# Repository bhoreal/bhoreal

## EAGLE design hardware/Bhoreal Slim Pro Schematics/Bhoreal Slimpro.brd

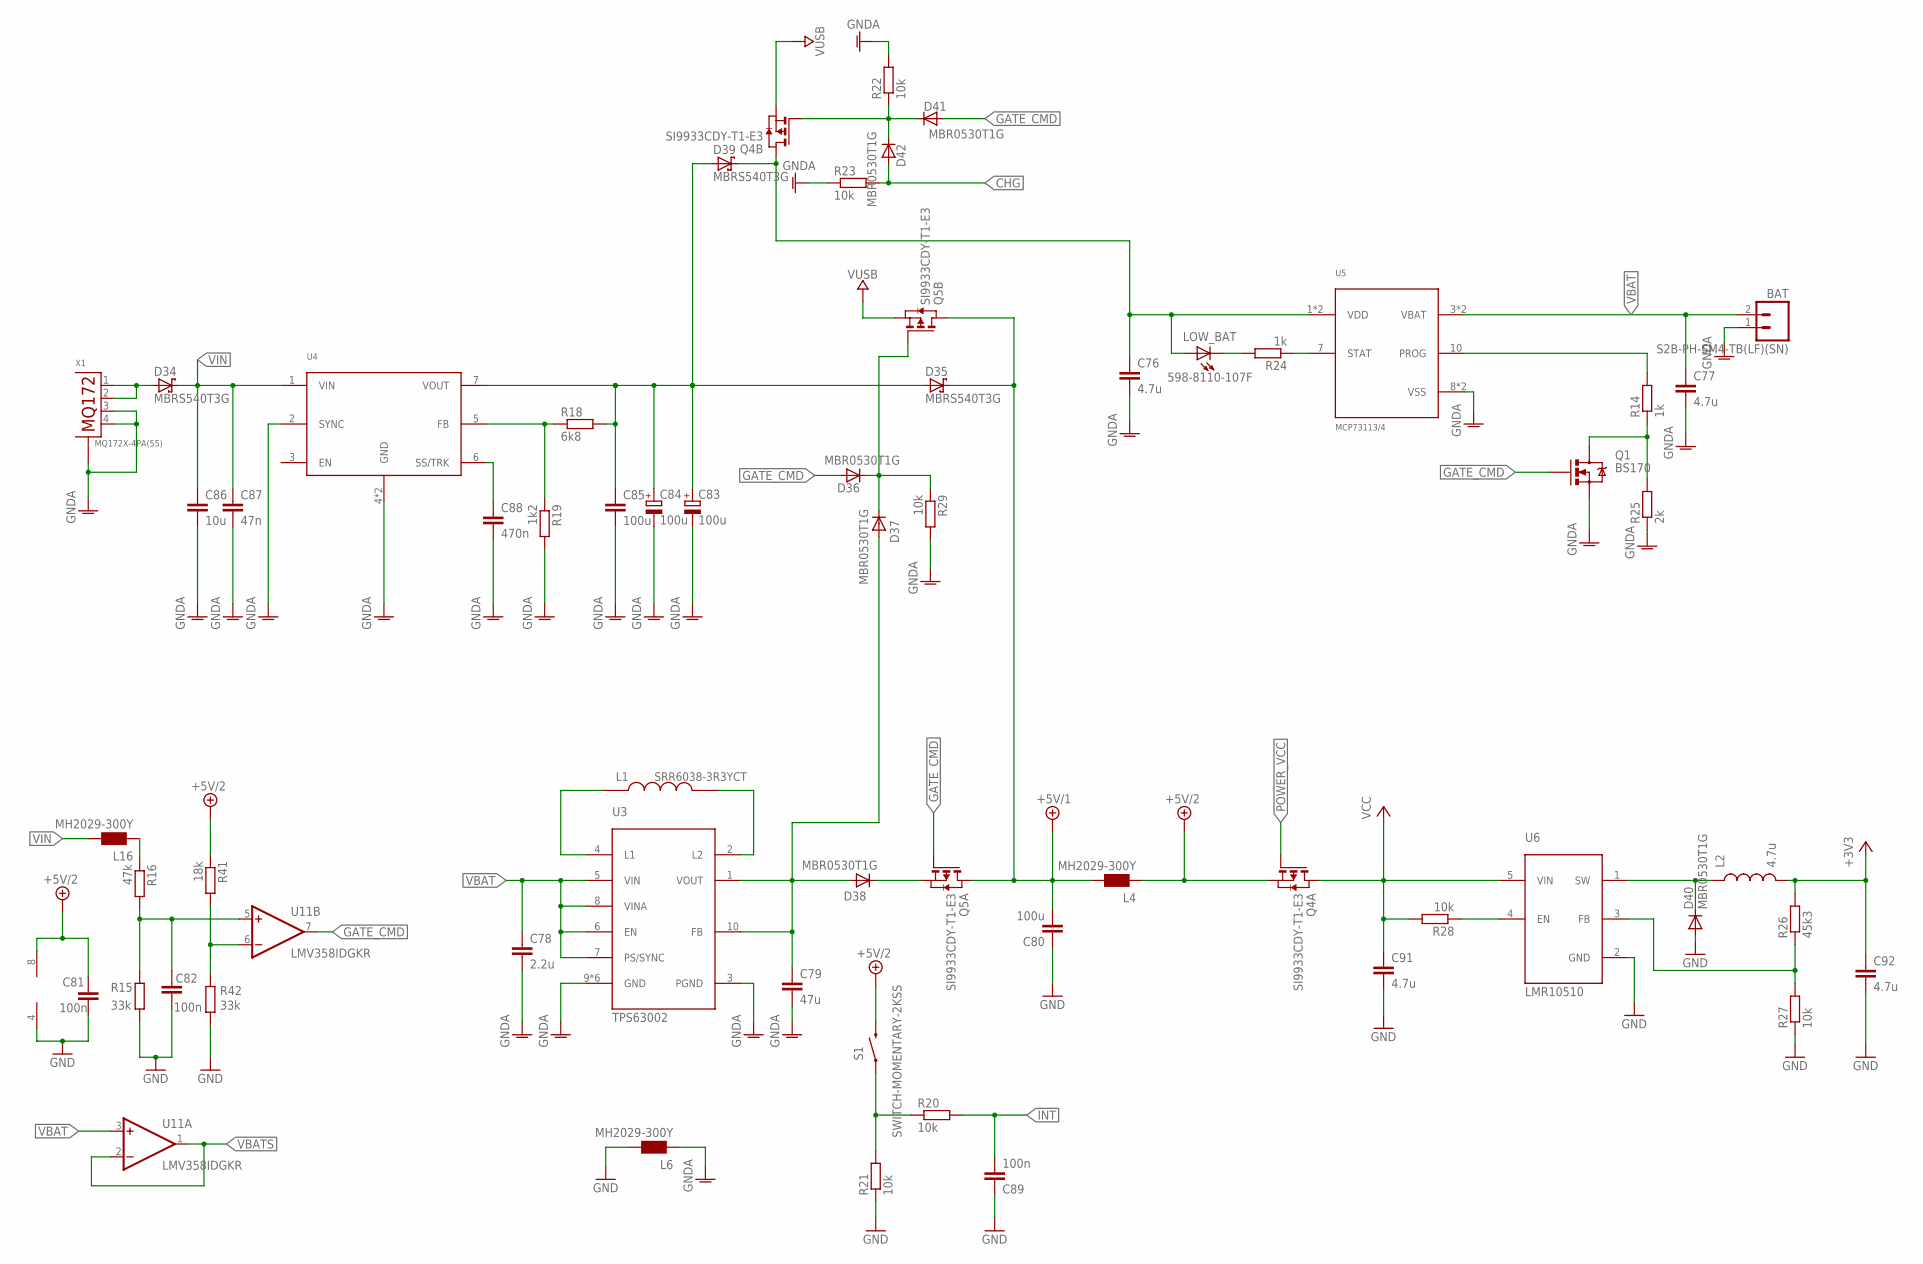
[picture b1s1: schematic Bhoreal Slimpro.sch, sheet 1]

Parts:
BAT: S2B-PH-SM4-TB(LF)(SN); S2B-PH
C76, C77: 4.7u; C0805
C78: 2.2u; C0805
C79: 47u; C1812
C80: 100u; C1206
C81, C82, C89: 100n; C0603
C83, C84: 100u; D/7343-31R
C85: 100u; C1210
C86: 10u; C1210
C87: 47n; C1206
C88: 470n; C0805
C91, C92: 4.7u; C0603
D34, D35, D39: MBRS540T3G; SMC
D36, D37, D38, D40, D41, D42: MBR0530T1G; SOD123
L1: SRR6038-3R3YCT; SRR6038
L2: 4.7u; 1210
L4, L6, L16: MH2029-300Y; 0805
LOW_BAT: 598-8110-107F; CHIP-LED0805
Q1: BS170; SOT23
Q4, Q5: SI9933CDY-T1-E3; SO8
R14, R24: 1k; R0603
R15, R42: 33k; R0603
R16: 47k; R0603
R18: 6k8; R0603
R19: 1k2; R0603
R20, R21, R22, R23, R27, R28, R29: 10k; R0603
R25: 2k; R0603
R26: 45k3; R0603
R41: 18k; R0603
S1: SWITCH-MOMENTARY-2KSS; KSS241G
U3: TPS63002; QFN-10_PAD
U4: LMZ2200X; TO-PMOD
U5: MCP73113/4; DFN-10
U6: LMR10510; SOT23-5L
U11: LMV358IDGKR; MSOP08
X1: MQ172X-4PA(55)

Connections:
+3V3: C92.1, L2.2, R26.2; also elsewhere on the board
+5V/1: C80.2, D35.C, L4.2, Q5.5 (D), Q5.6 (D), Q5.7 (D), Q5.8 (D); also elsewhere on the board
+5V/2: C81.1, L4.1, Q4.1 (S), R41.1, S1.2, U11.8 (V+); also elsewhere on the board
CHG: D42.A, R23.2; also elsewhere on the board
CMP: C82.2, R15.1, R16.2, U11.5 (+IN)
GATE_CMD: D36.A, D41.A, Q1.1 (G), Q5.2 (G), U11.7 (OUT); also elsewhere on the board
GND: C80.1, C81.2, C82.1, C89.1, C91.2, C92.2, D40.A, L6.2, R15.2, R21.1, R27.1, R42.2, U6.2 (GND), U11.4 (V-); also elsewhere on the board
GNDA: BAT.1, C76.2, C77.2, C78.2, C79.2, C83.-, C84.-, C85.2, C86.2, C87.2, C88.2, L6.1, Q1.2 (S), R19.2, R22.2, R23.1, R25.1, R29.2, U3.3 (PGND), U3.9 (GND), U3.11 (GND), U3.12 (GND), U3.13 (GND), U3.14 (GND), U3.15 (GND), U4.2 (SYNC), U4.4 (GND), U4.8 (GND), U5.8 (VSS), U5.9 (VSS), X1.3, X1.4, X1.P$1, X1.P$2; also elsewhere on the board
INT: C89.2, R20.2; also elsewhere on the board
unnamed: R41.2, R42.1, U11.6 (-IN)
unnamed: D41.C, D42.C, Q4.4 (G), R22.1
unnamed: R14.2, U5.10 (PROG)
unnamed: L1.P$1 (1), U3.4 (L1)
unnamed: L1.P$2 (2), U3.2 (L2)
unnamed: D34.A, X1.1, X1.2
unnamed: C79.1, D37.A, D38.A, U3.1 (VOUT), U3.10 (FB)
unnamed: C76.1, D39.C, LOW_BAT.A, Q4.5 (D), Q4.6 (D), U5.1 (VDD), U5.2 (VDD)
unnamed: C83.+, C84.+, C85.1, D35.A, D39.A, R18.2, U4.7 (VOUT)
unnamed: R18.1, R19.1, U4.5 (FB)
unnamed: C88.1, U4.6 (SS/TRK)
unnamed: R20.1, R21.2, S1.1
unnamed: D36.C, D37.C, Q5.4 (G), R29.1
unnamed: LOW_BAT.C, R24.2
unnamed: R24.1, U5.7 (STAT)
unnamed: Q1.3 (D), R14.1, R25.2
unnamed: D40.C, L2.1, U6.1 (SW)
unnamed: R28.1, U6.4 (EN)
unnamed: R26.1, R27.2, U6.3 (FB)
unnamed: D38.C, Q5.1 (S)
unnamed: L16.1, R16.1
POWER_VCC: Q4.2 (G); also elsewhere on the board
VBAT: BAT.2, C77.1, C78.1, U3.5 (VIN), U3.6 (EN), U3.7 (PS/SYNC), U3.8 (VINA), U5.3 (VBAT), U5.4 (VBAT), U11.3 (+IN)
VBATS: U11.1 (OUT), U11.2 (-IN); also elsewhere on the board
VCC: C91.1, Q4.7 (D), Q4.8 (D), R28.2, U6.5 (VIN); also elsewhere on the board
VIN: C86.1, C87.1, D34.C, L16.2, U4.1 (VIN)
VUSB: Q4.3 (S), Q5.3 (S); also elsewhere on the board

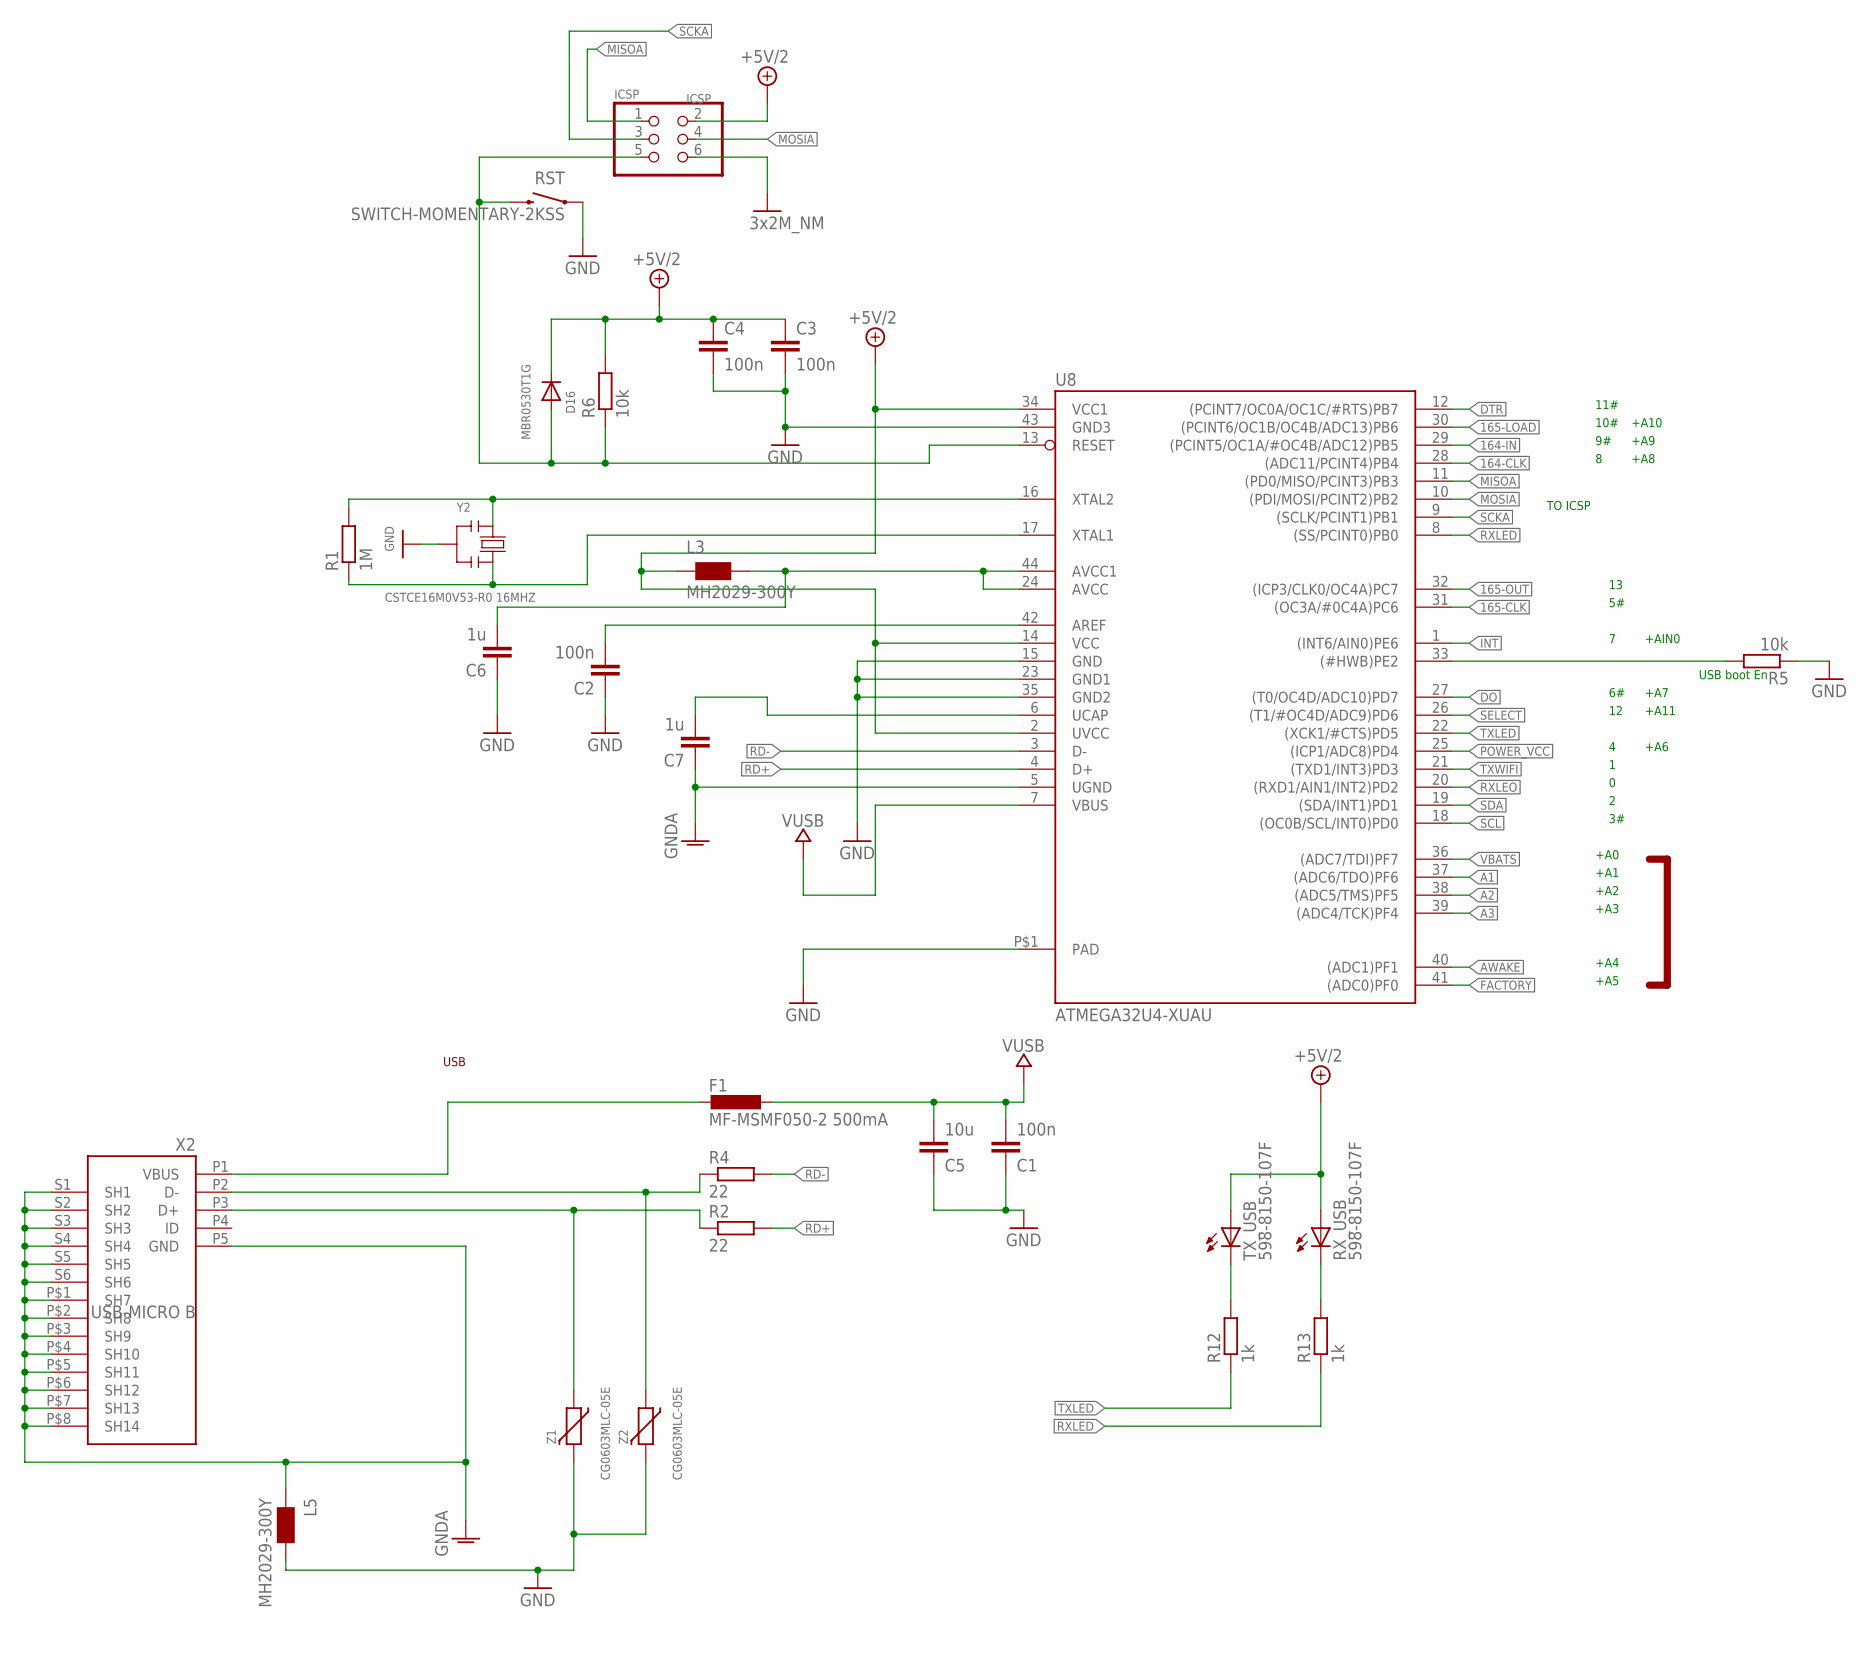
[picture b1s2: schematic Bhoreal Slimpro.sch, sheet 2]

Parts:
C1, C2, C3, C4: 100n; C0603
C5: 10u; C0805
C6, C7: 1u; C0805
D16: MBR0530T1G; SOD123
F1: MF-MSMF050-2 500mA; L1812
ICSP: ICSP; 2X03
L3, L5: MH2029-300Y; 0805
R1: 1M; R0603
R2, R4: 22; R0603
R5, R6: 10k; R0603
R12, R13: 1k; R0603
RST: SWITCH-MOMENTARY-2KSS; KSS241G
RX_USB: 598-8150-107F; CHIPLED_0805
TX_USB: 598-8150-107F; CHIPLED_0805
U8: ATMEGA32U4-XUAU; TQFP44-PAD
X2: USB-MICRO B; CON2_USB_MICRO_B_AT
Y2: CSTCE16M0V53-R0 16MHZ; RESONATOR
Z1, Z2: CG0603MLC-05E; CT/CN0603

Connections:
164-CLK: U8.28 ((ADC11/PCINT4)PB4); also elsewhere on the board
164-IN: U8.29 ((PCINT5/OC1A/#OC4B/ADC12)PB5); also elsewhere on the board
165-CLK: U8.31 ((OC3A/#0C4A)PC6); also elsewhere on the board
165-LOAD: U8.30 ((PCINT6/OC1B/OC4B/ADC13)PB6); also elsewhere on the board
165-OUT: U8.32 ((ICP3/CLK0/OC4A)PC7); also elsewhere on the board
+5V/2: C3.1, C4.1, D16.C, ICSP.2, L3.1, R6.2, RX_USB.A, TX_USB.A, U8.2 (UVCC), U8.14 (VCC), U8.34 (VCC1); also elsewhere on the board
A1: U8.37 ((ADC6/TDO)PF6)
A2: U8.38 ((ADC5/TMS)PF5)
A3: U8.39 ((ADC4/TCK)PF4)
AREF: C2.2, U8.42 (AREF)
AVCC: C6.2, L3.2, U8.24 (AVCC), U8.44 (AVCC1)
AWAKE: U8.40 ((ADC1)PF1); also elsewhere on the board
D+: R2.1, X2.P3 (D+), Z1.1
D-: R4.1, X2.P2 (D-), Z2.1
DO: U8.27 ((T0/OC4D/ADC10)PD7); also elsewhere on the board
DTR: U8.12 ((PCINT7/OC0A/OC1C/#RTS)PB7); also elsewhere on the board
FACTORY: U8.41 ((ADC0)PF0); also elsewhere on the board
GND: C1.1, C2.1, C3.2, C4.2, C5.1, C6.1, ICSP.6, L5.2, R5.1, RST.1, U8.15 (GND), U8.23 (GND1), U8.35 (GND2), U8.43 (GND3), U8.P$1 (PAD), Y2.2, Z1.2, Z2.2; also elsewhere on the board
GNDA: C7.1, L5.1, U8.5 (UGND), X2.P5 (GND), X2.P$1 (SH7), X2.P$2 (SH8), X2.P$3 (SH9), X2.P$4 (SH10), X2.P$5 (SH11), X2.P$6 (SH12), X2.P$7 (SH13), X2.P$8 (SH14), X2.S1 (SH1), X2.S2 (SH2), X2.S3 (SH3), X2.S4 (SH4), X2.S5 (SH5), X2.S6 (SH6); also elsewhere on the board
HWB: R5.2, U8.33 ((#HWB)PE2)
INT: U8.1 ((INT6/AIN0)PE6); also elsewhere on the board
MISOA: ICSP.1, U8.11 ((PD0/MISO/PCINT3)PB3)
MOSIA: ICSP.4, U8.10 ((PDI/MOSI/PCINT2)PB2)
unnamed: R12.2, TX_USB.C
unnamed: R13.2, RX_USB.C
POWER_VCC: U8.25 ((ICP1/ADC8)PD4); also elsewhere on the board
RD+: R2.2, U8.4 (D+)
RD-: R4.2, U8.3 (D-)
RST: D16.A, ICSP.5, R6.1, RST.2, U8.13 (RESET); also elsewhere on the board
RXLED: R13.1, U8.8 ((SS/PCINT0)PB0)
RXLEO: U8.20 ((RXD1/AIN1/INT2)PD2); also elsewhere on the board
SCKA: ICSP.3, U8.9 ((SCLK/PCINT1)PB1)
SCL: U8.18 ((OC0B/SCL/INT0)PD0); also elsewhere on the board
SDA: U8.19 ((SDA/INT1)PD1); also elsewhere on the board
SELECT: U8.26 ((T1/#OC4D/ADC9)PD6); also elsewhere on the board
TXLED: R12.1, U8.22 ((XCK1/#CTS)PD5)
TXWIFI: U8.21 ((TXD1/INT3)PD3); also elsewhere on the board
UCAP: C7.2, U8.6 (UCAP)
VBATS: U8.36 ((ADC7/TDI)PF7); also elsewhere on the board
VUSB: C1.2, C5.2, F1.1, U8.7 (VBUS); also elsewhere on the board
XTAL3: R1.2, U8.16 (XTAL2), Y2.1
XTAL4: R1.1, U8.17 (XTAL1), Y2.3
XUSB: F1.2, X2.P1 (VBUS)

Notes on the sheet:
USB boot En
USB
TO ICSP
10#
11#
+A6
+A11
+A10
+A9
+A7
+A8
+AIN0
+A0
+A1
+A2
+A3
+A4
+A5

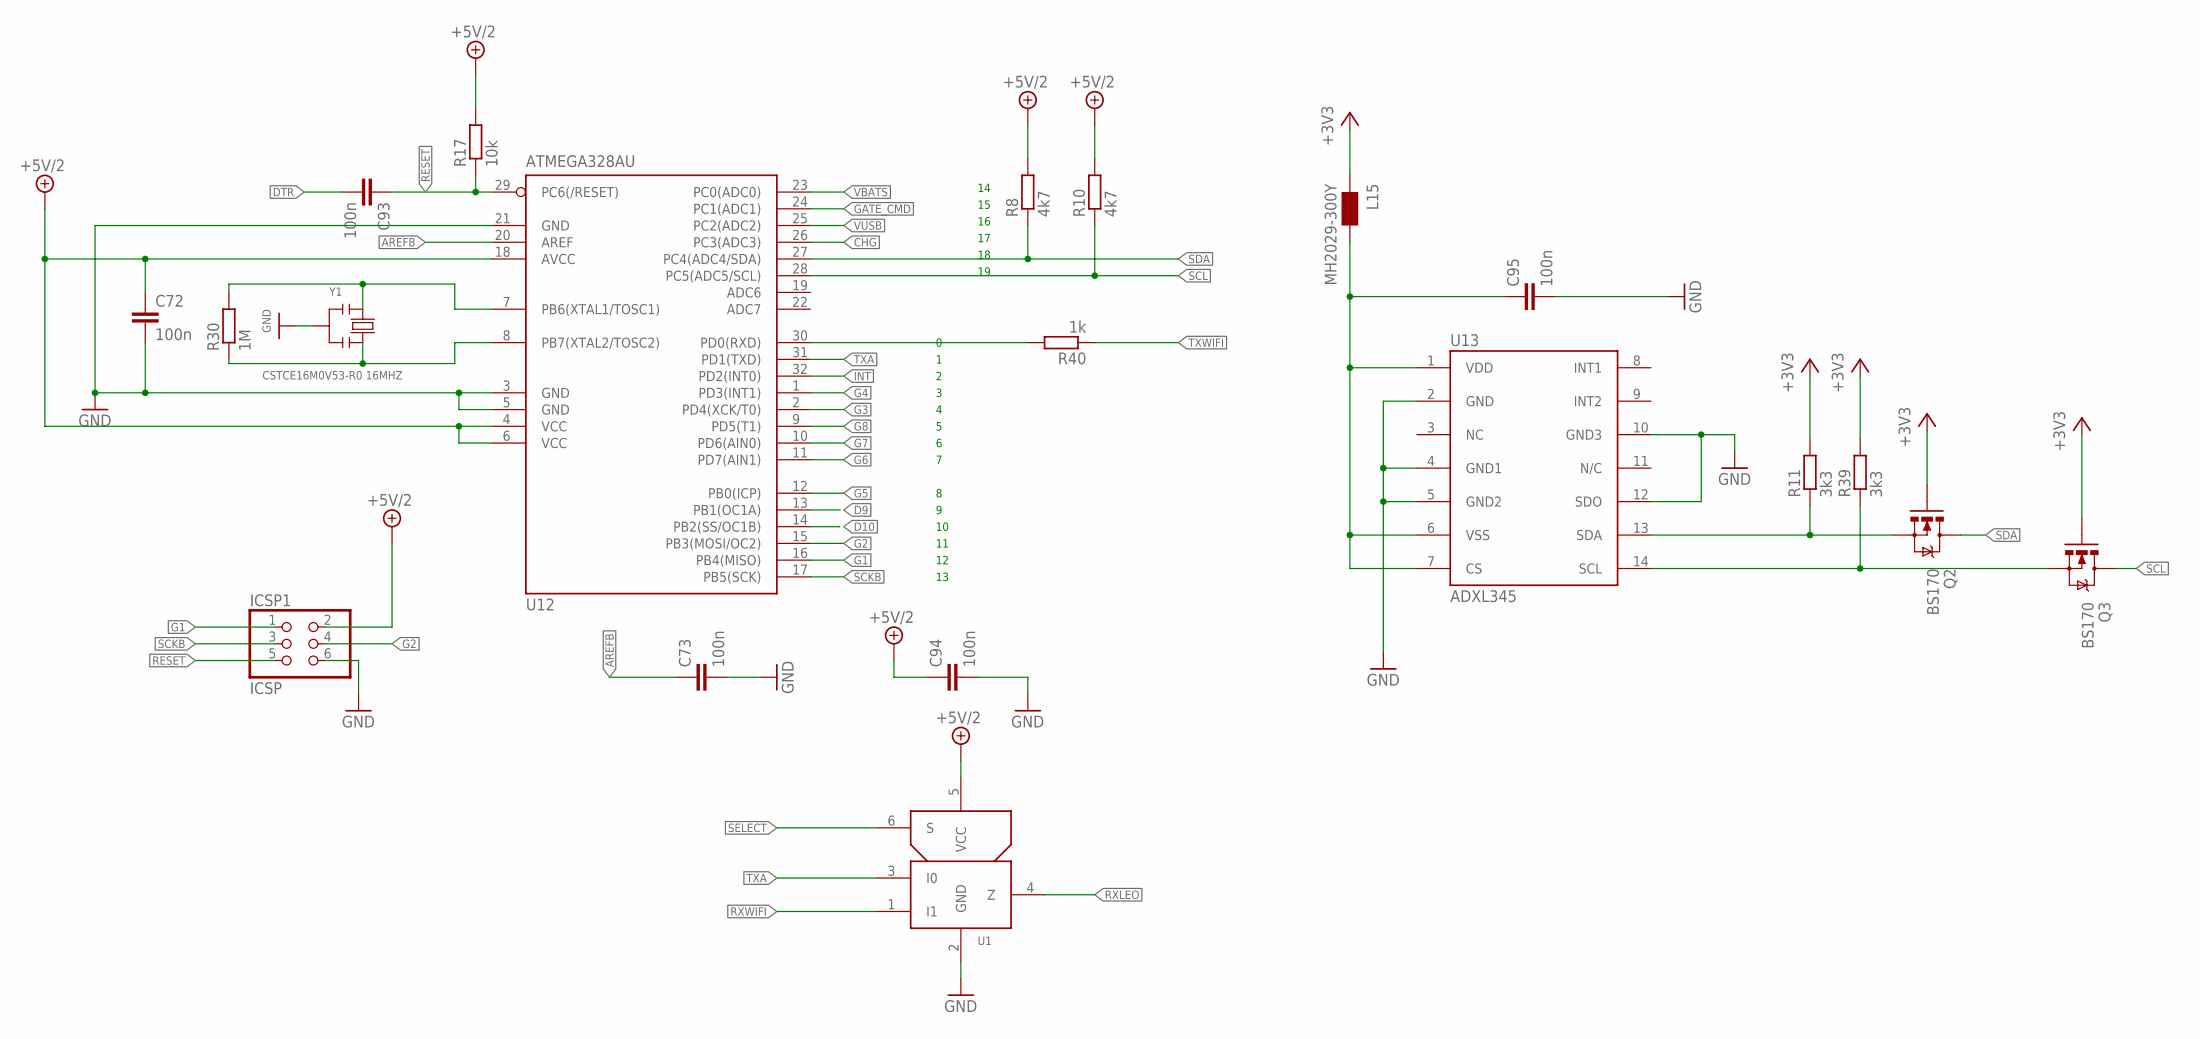
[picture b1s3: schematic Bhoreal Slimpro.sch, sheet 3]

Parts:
C72, C73, C93, C94, C95: 100n; C0603
ICSP1: ICSP; 2X03
L15: MH2029-300Y; 0805
Q2, Q3: BS170; SOT23
R8, R10: 4k7; R0603
R11, R39: 3k3; R0603
R17: 10k; R0603
R30: 1M; R0603
R40: 1k; R0603
U1: NC7SZ157P6X; SC70
U12: ATMEGA328AU; TQFP32-08
U13: ADXL345; LGA14
Y1: CSTCE16M0V53-R0 16MHZ; RESONATOR

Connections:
+3V3: L15.1, Q2.1 (G), Q3.1 (G), R11.2, R39.2; also elsewhere on the board
+5V/2: C72.1, C94.1, ICSP1.2, R8.2, R10.2, R17.2, U1.5 (VCC), U12.4 (VCC), U12.6 (VCC), U12.18 (AVCC); also elsewhere on the board
AREFB: C73.1, U12.20 (AREF)
CHG: U12.26 (PC3(ADC3)); also elsewhere on the board
D9: U12.13 (PB1(OC1A))
D10: U12.14 (PB2(SS/OC1B))
DTR: C93.2; also elsewhere on the board
G1: ICSP1.1, U12.16 (PB4(MISO)); also elsewhere on the board
G2: ICSP1.4, U12.15 (PB3(MOSI/OC2)); also elsewhere on the board
G3: U12.2 (PD4(XCK/T0)); also elsewhere on the board
G4: U12.1 (PD3(INT1)); also elsewhere on the board
G5: U12.12 (PB0(ICP)); also elsewhere on the board
G6: U12.11 (PD7(AIN1)); also elsewhere on the board
G7: U12.10 (PD6(AIN0)); also elsewhere on the board
G8: U12.9 (PD5(T1)); also elsewhere on the board
GATE_CMD: U12.24 (PC1(ADC1)); also elsewhere on the board
GND: C72.2, C73.2, C94.2, C95.2, ICSP1.6, U1.2 (GND), U12.3 (GND), U12.5 (GND), U12.21 (GND), U13.2 (GND), U13.4 (GND1), U13.5 (GND2), U13.10 (GND3), U13.12 (SDO), Y1.2; also elsewhere on the board
INT: U12.32 (PD2(INT0)); also elsewhere on the board
unnamed: C95.1, L15.2, U13.1 (VDD), U13.6 (VSS), U13.7 (CS)
unnamed: Q2.2 (S), R11.1, U13.13 (SDA)
unnamed: Q3.2 (S), R39.1, U13.14 (SCL)
RESET: C93.1, ICSP1.5, R17.1, U12.29 (PC6(/RESET))
RXA: R40.2, U12.30 (PD0(RXD))
RXLEO: U1.4 (Z); also elsewhere on the board
RXWIFI: U1.1 (I1); also elsewhere on the board
SCKB: ICSP1.3, U12.17 (PB5(SCK))
SCL: Q3.3 (D), R10.1, U12.28 (PC5(ADC5/SCL)); also elsewhere on the board
SDA: Q2.3 (D), R8.1, U12.27 (PC4(ADC4/SDA)); also elsewhere on the board
SELECT: U1.6 (S); also elsewhere on the board
TXA: U1.3 (I0), U12.31 (PD1(TXD))
TXWIFI: R40.1; also elsewhere on the board
VBATS: U12.23 (PC0(ADC0)); also elsewhere on the board
VUSB: U12.25 (PC2(ADC2)); also elsewhere on the board
XTAL1: R30.2, U12.7 (PB6(XTAL1/TOSC1)), Y1.1
XTAL2: R30.1, U12.8 (PB7(XTAL2/TOSC2)), Y1.3

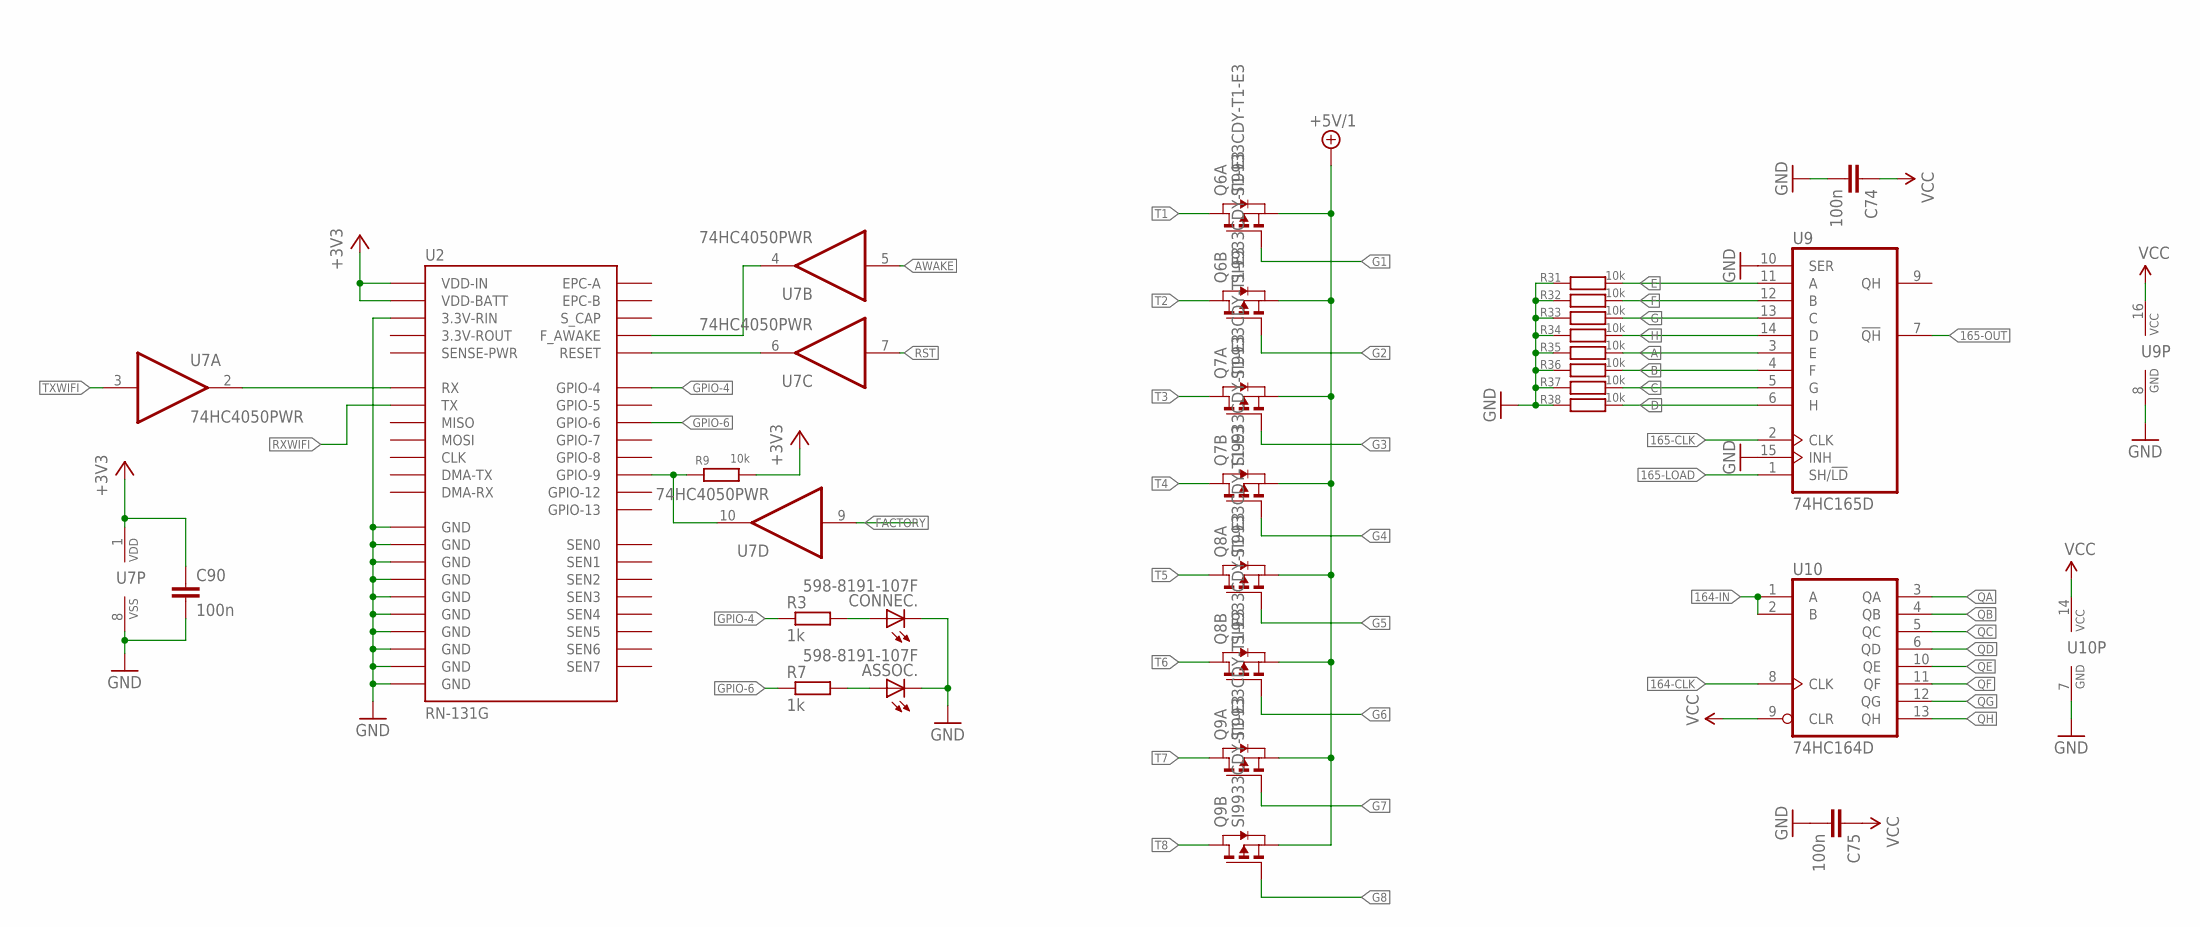
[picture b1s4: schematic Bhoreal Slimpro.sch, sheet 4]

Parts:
ASSOC.: 598-8191-107F; CHIP-LED0805
C74, C75, C90: 100n; C0603
CONNEC.: 598-8191-107F; CHIP-LED0805
Q6, Q7, Q8, Q9: SI9933CDY-T1-E3; SO8
R3, R7: 1k; R0603
R9, R31, R32, R33, R34, R35, R36, R37, R38: 10k; R0603
U2: RN-131G
U7: 74HC4050PWR; TSSOP16
U9: 74HC165D; SO16
U10: 74HC164D; SO14

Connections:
164-CLK: U10.8 (CLK); also elsewhere on the board
164-IN: U10.1 (A), U10.2 (B); also elsewhere on the board
165-CLK: U9.2 (CLK); also elsewhere on the board
165-LOAD: U9.1 (SH/!LD); also elsewhere on the board
165-OUT: U9.7 (!QH); also elsewhere on the board
+3V3: C90.1, R9.2, U2.P$20 (VDD-BATT), U2.P$21 (VDD-IN), U7.1 (VDD); also elsewhere on the board
+5V/1: Q6.1 (S), Q6.3 (S), Q7.1 (S), Q7.3 (S), Q8.1 (S), Q8.3 (S), Q9.1 (S), Q9.3 (S); also elsewhere on the board
A: R35.2, U9.3 (E); also elsewhere on the board
AWAKE: U7.5 (I); also elsewhere on the board
B: R36.2, U9.4 (F); also elsewhere on the board
C: R37.2, U9.5 (G); also elsewhere on the board
D: R38.2, U9.6 (H); also elsewhere on the board
E: R31.2, U9.11 (A); also elsewhere on the board
F: R32.2, U9.12 (B); also elsewhere on the board
FACTORY: U7.9 (I); also elsewhere on the board
G: R33.2, U9.13 (C); also elsewhere on the board
G1: Q6.2 (G); also elsewhere on the board
G2: Q6.4 (G); also elsewhere on the board
G3: Q7.2 (G); also elsewhere on the board
G4: Q7.4 (G); also elsewhere on the board
G5: Q8.2 (G); also elsewhere on the board
G6: Q8.4 (G); also elsewhere on the board
G7: Q9.2 (G); also elsewhere on the board
G8: Q9.4 (G); also elsewhere on the board
GND: ASSOC..C, C74.2, C75.2, C90.2, CONNEC..C, R31.1, R32.1, R33.1, R34.1, R35.1, R36.1, R37.1, R38.1, U2.P$18 (3.3V-RIN), U2.P$19 (GND), U2.P$36 (GND), U2.P$37 (GND), U2.P$38 (GND), U2.P$39 (GND), U2.P$40 (GND), U2.P$41 (GND), U2.P$42 (GND), U2.P$43 (GND), U2.P$44 (GND), U7.8 (VSS), U9.8 (GND), U9.10 (SER), U9.15 (INH), U10.7 (GND); also elsewhere on the board
GPIO-4: R3.1, U2.P$29 (GPIO-4)
GPIO-6: R7.1, U2.P$27 (GPIO-6)
H: R34.2, U9.14 (D); also elsewhere on the board
unnamed: CONNEC..A, R3.2
unnamed: ASSOC..A, R7.2
unnamed: U2.P$12 (RX), U7.2 (O)
unnamed: R9.1, U2.P$24 (GPIO-9), U7.10 (O)
unnamed: U2.P$9 (F_AWAKE), U7.4 (O)
unnamed: U2.P$5 (RESET), U7.6 (O)
QA: U10.3 (QA); also elsewhere on the board
QB: U10.4 (QB); also elsewhere on the board
QC: U10.5 (QC); also elsewhere on the board
QD: U10.6 (QD); also elsewhere on the board
QE: U10.10 (QE); also elsewhere on the board
QF: U10.11 (QF); also elsewhere on the board
QG: U10.12 (QG); also elsewhere on the board
QH: U10.13 (QH); also elsewhere on the board
RST: U7.7 (I); also elsewhere on the board
RXWIFI: U2.P$13 (TX); also elsewhere on the board
T1: Q6.7 (D), Q6.8 (D); also elsewhere on the board
T2: Q6.5 (D), Q6.6 (D); also elsewhere on the board
T3: Q7.7 (D), Q7.8 (D); also elsewhere on the board
T4: Q7.5 (D), Q7.6 (D); also elsewhere on the board
T5: Q8.7 (D), Q8.8 (D); also elsewhere on the board
T6: Q8.5 (D), Q8.6 (D); also elsewhere on the board
T7: Q9.7 (D), Q9.8 (D); also elsewhere on the board
T8: Q9.5 (D), Q9.6 (D); also elsewhere on the board
TXWIFI: U7.3 (I); also elsewhere on the board
VCC: C74.1, C75.1, U9.16 (VCC), U10.9 (CLR), U10.14 (VCC); also elsewhere on the board

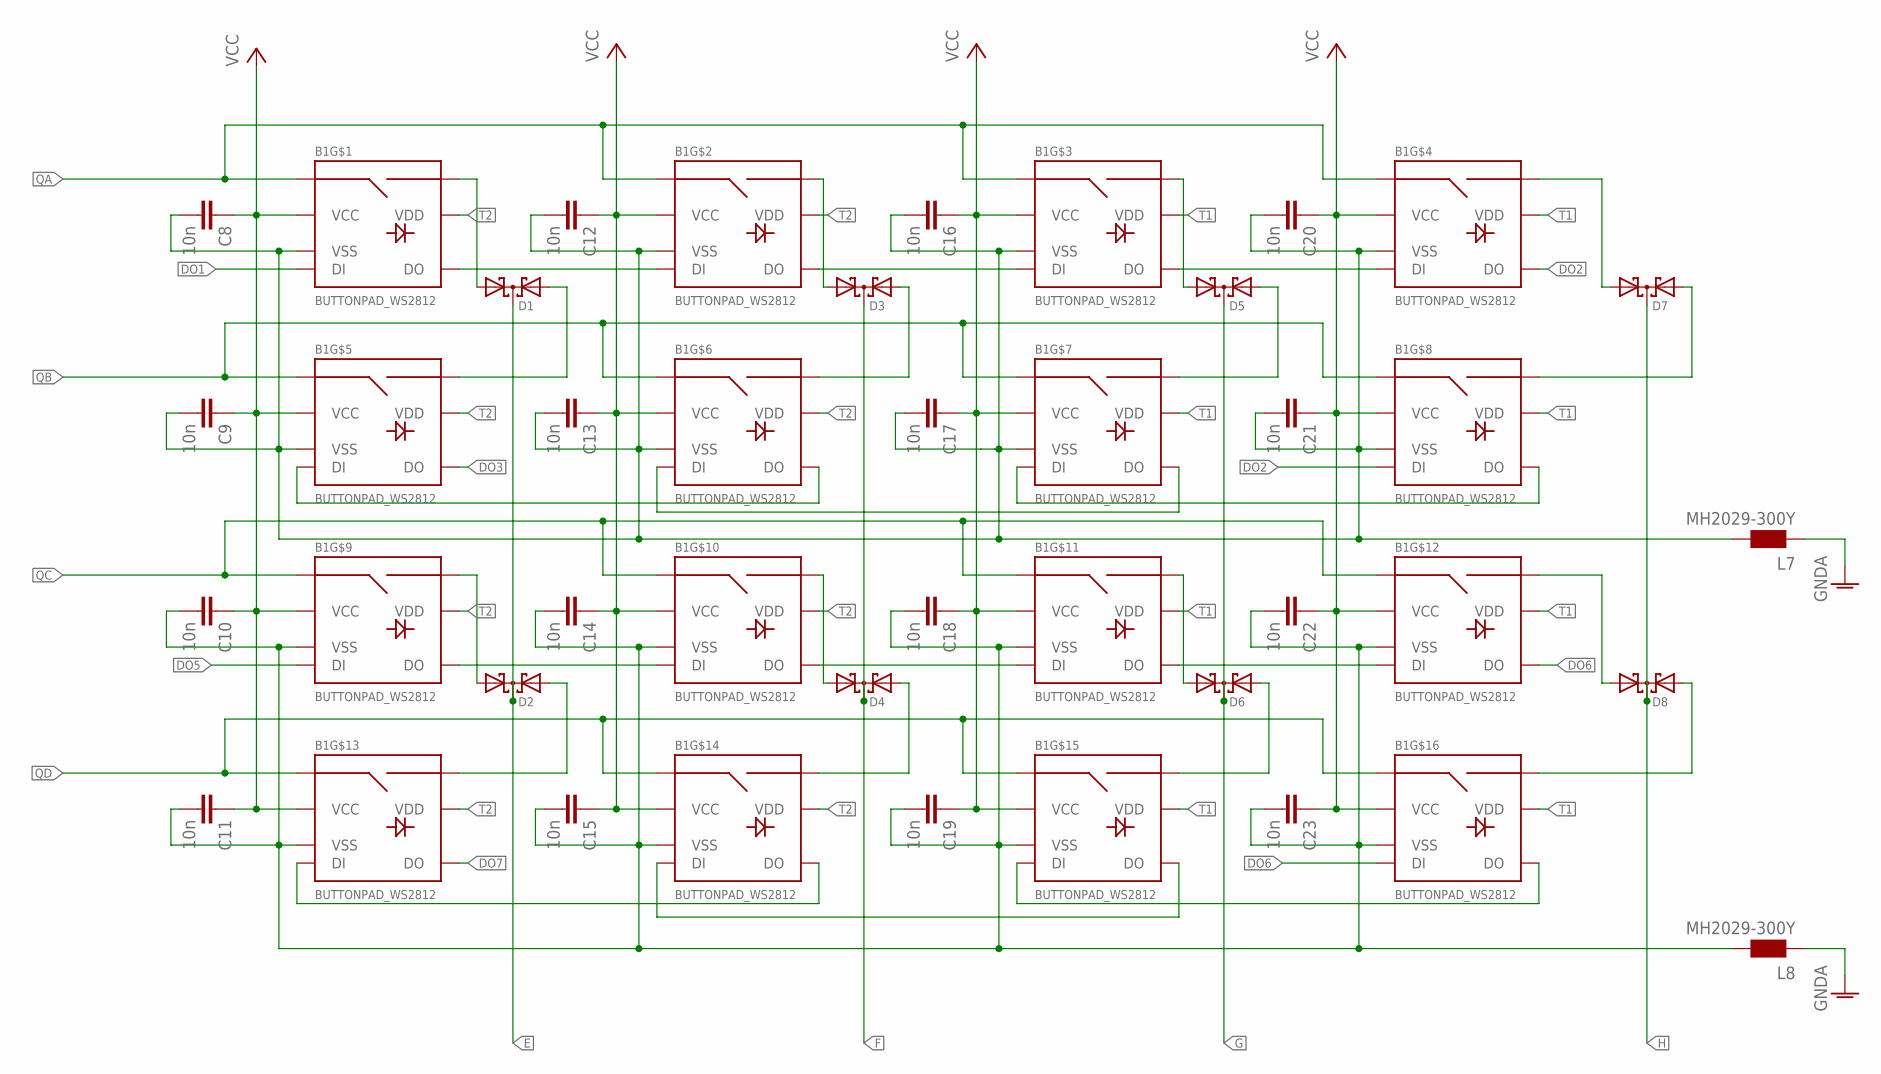
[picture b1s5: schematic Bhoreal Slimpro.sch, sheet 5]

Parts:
B1: BUTTONPAD_WS2812
C8, C9, C10, C11, C12, C13, C14, C15, C16, C17, C18, C19, C20, C21, C22, C23: 10n; C0603
D1, D2, D3, D4, D5, D6, D7, D8: BAV70LT3G; SOT23
L7, L8: MH2029-300Y; 0805

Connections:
DO1: B1.2A (DI); also elsewhere on the board
DO2: B1.1D (DO), B1.2H (DI)
DO3: B1.1E (DO); also elsewhere on the board
DO5: B1.2I (DI); also elsewhere on the board
DO6: B1.1L (DO), B1.2P (DI)
DO7: B1.1M (DO); also elsewhere on the board
E: D1.3 (C), D2.3 (C); also elsewhere on the board
F: D3.3 (C), D4.3 (C); also elsewhere on the board
G: D5.3 (C), D6.3 (C); also elsewhere on the board
GNDA: L7.1, L8.1; also elsewhere on the board
H: D7.3 (C), D8.3 (C); also elsewhere on the board
unnamed: B1.SIG2A (SIG2), D1.1 (A1)
unnamed: B1.SIG2E (SIG2), D1.2 (A2)
unnamed: B1.SIG2I (SIG2), D2.1 (A1)
unnamed: B1.SIG2M (SIG2), D2.2 (A2)
unnamed: B1.SIG2B (SIG2), D3.1 (A1)
unnamed: B1.SIG2F (SIG2), D3.2 (A2)
unnamed: B1.SIG2J (SIG2), D4.1 (A1)
unnamed: B1.SIG2N (SIG2), D4.2 (A2)
unnamed: B1.SIG2C (SIG2), D5.1 (A1)
unnamed: B1.SIG2G (SIG2), D5.2 (A2)
unnamed: B1.SIG2K (SIG2), D6.1 (A1)
unnamed: B1.SIG2O (SIG2), D6.2 (A2)
unnamed: B1.SIG2L (SIG2), D8.1 (A1)
unnamed: B1.SIG2P (SIG2), D8.2 (A2)
unnamed: B1.SIG2D (SIG2), D7.1 (A1)
unnamed: B1.SIG2H (SIG2), D7.2 (A2)
unnamed: B1.1A (DO), B1.2B (DI)
unnamed: B1.1F (DO), B1.2E (DI)
unnamed: B1.1G (DO), B1.2F (DI)
unnamed: B1.1B (DO), B1.2C (DI)
unnamed: B1.1C (DO), B1.2D (DI)
unnamed: B1.1H (DO), B1.2G (DI)
unnamed: B1.1K (DO), B1.2L (DI)
unnamed: B1.1J (DO), B1.2K (DI)
unnamed: B1.1I (DO), B1.2J (DI)
unnamed: B1.1P (DO), B1.2O (DI)
unnamed: B1.1O (DO), B1.2N (DI)
unnamed: B1.1N (DO), B1.2M (DI)
unnamed: B1.6A (VSS), B1.6B (VSS), B1.6C (VSS), B1.6D (VSS), B1.6E (VSS), B1.6F (VSS), B1.6G (VSS), B1.6H (VSS), C8.2, C9.2, C12.2, C13.2, C16.2, C17.2, C20.2, C21.2, L7.2
unnamed: B1.6I (VSS), B1.6J (VSS), B1.6K (VSS), B1.6L (VSS), B1.6M (VSS), B1.6N (VSS), B1.6O (VSS), B1.6P (VSS), C10.2, C11.2, C14.2, C15.2, C18.2, C19.2, C22.2, C23.2, L8.2
QA: B1.SIG1A (SIG1), B1.SIG1B (SIG1), B1.SIG1C (SIG1), B1.SIG1D (SIG1); also elsewhere on the board
QB: B1.SIG1E (SIG1), B1.SIG1F (SIG1), B1.SIG1G (SIG1), B1.SIG1H (SIG1); also elsewhere on the board
QC: B1.SIG1I (SIG1), B1.SIG1J (SIG1), B1.SIG1K (SIG1), B1.SIG1L (SIG1); also elsewhere on the board
QD: B1.SIG1M (SIG1), B1.SIG1N (SIG1), B1.SIG1O (SIG1), B1.SIG1P (SIG1); also elsewhere on the board
T1: B1.5C (VDD), B1.5D (VDD), B1.5G (VDD), B1.5H (VDD), B1.5K (VDD), B1.5L (VDD), B1.5O (VDD), B1.5P (VDD); also elsewhere on the board
T2: B1.5A (VDD), B1.5B (VDD), B1.5E (VDD), B1.5F (VDD), B1.5I (VDD), B1.5J (VDD), B1.5M (VDD), B1.5N (VDD); also elsewhere on the board
VCC: B1.3A (VCC), B1.3B (VCC), B1.3C (VCC), B1.3D (VCC), B1.3E (VCC), B1.3F (VCC), B1.3G (VCC), B1.3H (VCC), B1.3I (VCC), B1.3J (VCC), B1.3K (VCC), B1.3L (VCC), B1.3M (VCC), B1.3N (VCC), B1.3O (VCC), B1.3P (VCC), C8.1, C9.1, C10.1, C11.1, C12.1, C13.1, C14.1, C15.1, C16.1, C17.1, C18.1, C19.1, C20.1, C21.1, C22.1, C23.1; also elsewhere on the board

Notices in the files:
parts and their libraries:
SparkFun-DiscreteSemi: Licensing: CC v3.0 Share-Alike You are welcome to use this library for commercial purposes.
